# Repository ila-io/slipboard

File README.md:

# slipboard
I designed this macropad to slip onto the top of my Surface Pro, since I like to take the keyboard off to draw and watch media in tablet mode, but I also like to be able to copy and paste, undo, and the like. The pen buttons are extremely unhelpful in their utility to say the least, so I created a macropad! As of now, the button layout is as such: 

| undo | copy | paste | delete |
| ---- | ---- | ----- | ------ | 

The encoder press is used to pause/play music, and as of now it's rotation just bound to f13/f14, which I'm hoping to make change my pen size in Krita! 

## CAD
Here's the slipboard slipped onto a mockup section of the Surface Pro! 

There are soft sliders in the insets to allow the device to slide on and off safely, and stay secured while in use!

### back/bottom

I left a slot here for an acrylic sheet to slide in, since I like the look of the PCB and I put a design on the silkscreen that I don't want covered up :3

### disassembled

## PCB/Schematic
I'm a big fan of the look of the raw traces on the PCB, so I utilized that and the silkscreen to make a design that will show through on the backside of the slipboard when its on my tablet! 

### [demo video!](https://youtu.be/LWUtzJrfr4w)

## BOM
| Quantity | Material               |
|----------|------------------------|
| 1        | Seeed XIAO RP2040      | 
| 1        | PCB                    |
| 1        | EC11 Rotary encoder    |
| 4        | MX-Style switches      |
| 4        | MX Keycaps             | 
| 1        | 3D printed Case (2pts) |
| 4        | M3x16mm screws         |
| 4        | M3X5X4 Heatset Inserts |

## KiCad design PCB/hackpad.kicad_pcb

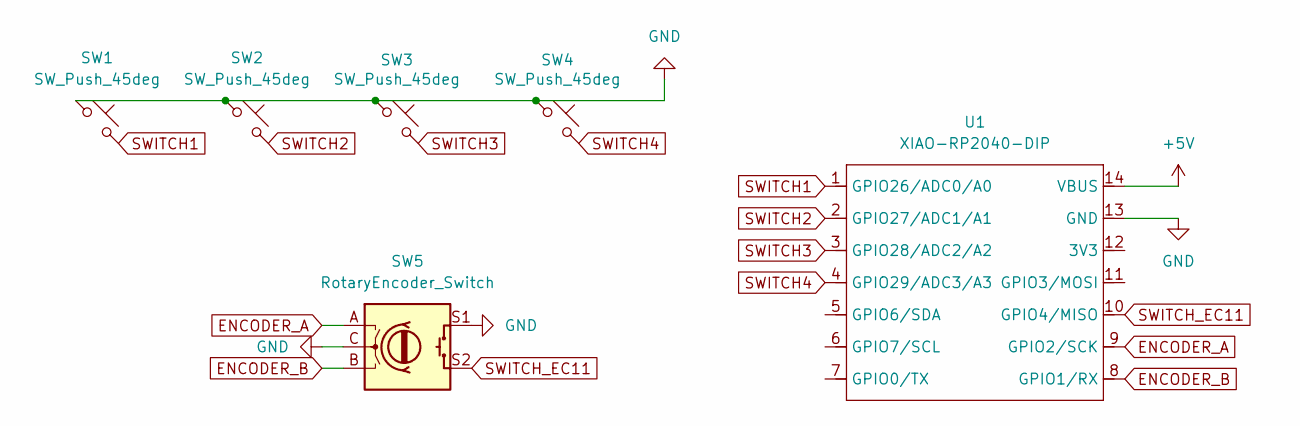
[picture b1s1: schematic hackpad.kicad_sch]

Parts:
SW1, SW2, SW3, SW4: SW_Push_45deg; SW_Cherry_MX_1.00u_PCB
SW5: RotaryEncoder_Switch; RotaryEncoder_Alps_EC11E-Switch_Vertical_H20mm
U1: XIAO-RP2040-DIP

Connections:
+5V: U1.14 (VBUS)
ENCODER_A: SW5.A, U1.9 (GPIO2/SCK)
ENCODER_B: SW5.B, U1.8 (GPIO1/RX)
GND: SW1.1, SW2.1, SW3.1, SW4.1, SW5.C, SW5.S1, U1.13 (GND)
SWITCH1: SW1.2, U1.1 (GPIO26/ADC0/A0)
SWITCH2: SW2.2, U1.2 (GPIO27/ADC1/A1)
SWITCH3: SW3.2, U1.3 (GPIO28/ADC2/A2)
SWITCH4: SW4.2, U1.4 (GPIO29/ADC3/A3)
SWITCH_EC11: SW5.S2, U1.10 (GPIO4/MISO)

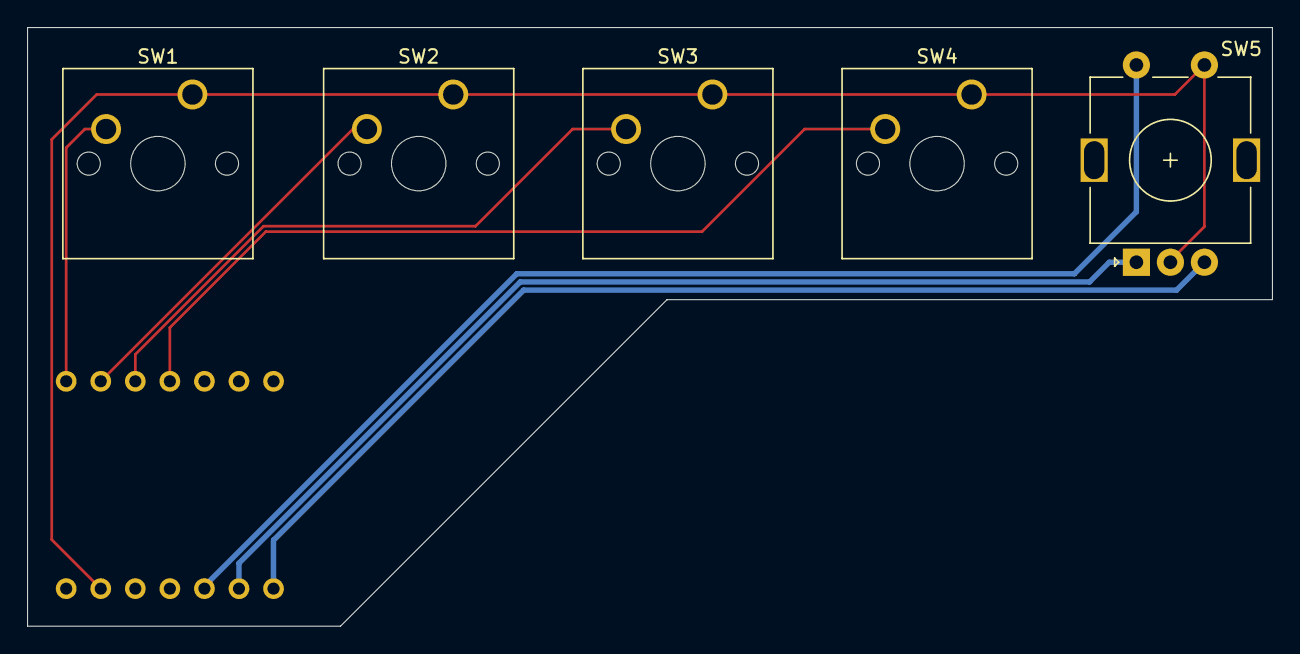
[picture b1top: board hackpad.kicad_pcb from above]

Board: 2 copper layers, 91.5 x 44.0 mm, 6 parts (1 on the bottom side), 8 nets.

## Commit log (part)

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2025-06-19 Add all files
2025-06-29 add cad photos to repo
